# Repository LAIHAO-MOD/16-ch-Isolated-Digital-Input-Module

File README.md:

# 16-ch-Isolated-Digital-Input-Module

16-ch isolated digital input module for DIY cnc system (MACH3 &amp; etc...)

Design for 12V inputs !!! Change input resistors before use in other voltage !!!

Use  KICAD 5.1 as Schematic & Pcb design software .

Production Gerber files will be  include after test run .

layout

3d rendering

pcb

assembled

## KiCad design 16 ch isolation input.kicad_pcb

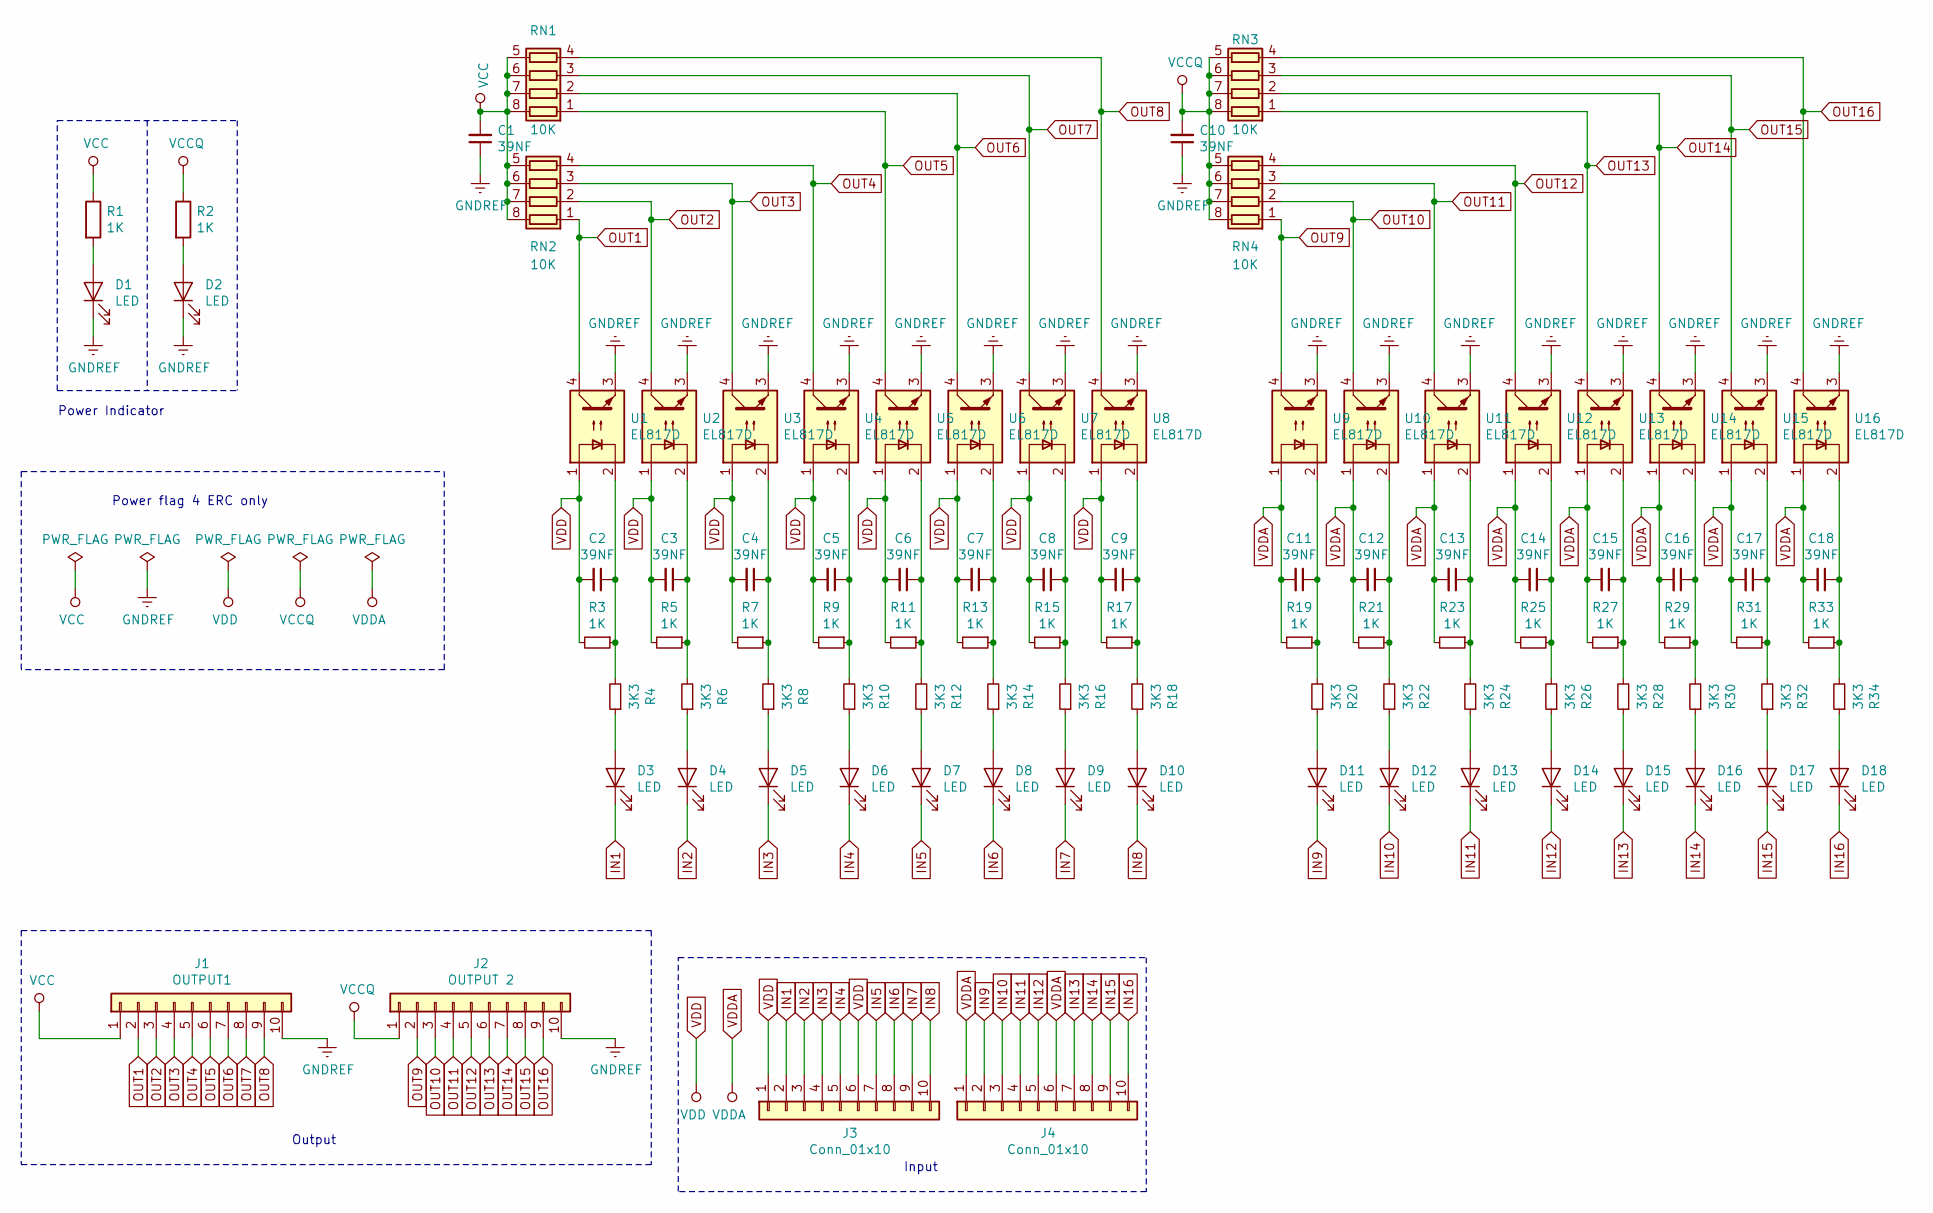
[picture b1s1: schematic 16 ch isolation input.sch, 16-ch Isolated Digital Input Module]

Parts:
C1, C2, C3, C4, C5, C6, C7, C8, C9, C10, C11, C12, C13, C14, C15, C16, C17, C18: 39NF; C_0603_1608Metric
D1, D2, D3, D4, D5, D6, D7, D8, D9, D10, D11, D12, D13, D14, D15, D16, D17, D18: LED; LED_1206_3216Metric
J1: OUTPUT1; mlx254
J2: OUTPUT 2; mlx254
J3, J4: Conn_01x10; ZIP-10-3.5-5
R1, R2, R3, R5, R7, R9, R11, R13, R15, R17, R19, R21, R23, R25, R27, R29, R31, R33: 1K; R_0603_1608Metric
R4, R6, R8, R10, R12, R14, R16, R18, R20, R22, R24, R26, R28, R30, R32, R34: 3K3; R_0603_1608Metric
RN1, RN2, RN3, RN4: 10K; R_Array_Convex_4x0603
U1, U2, U3, U4, U5, U6, U7, U8, U9, U10, U11, U12, U13, U14, U15, U16: EL817D; DIP-4_W7.62mm

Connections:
GNDREF: C1.1, C10.1, D1.1 (K), D2.1 (K), J1.10, J2.10, U1.3, U2.3, U3.3, U4.3, U5.3, U6.3, U7.3, U8.3, U9.3, U10.3, U11.3, U12.3, U13.3, U14.3, U15.3, U16.3; also elsewhere on the board
IN1: D3.1 (K), J3.2; also elsewhere on the board
IN2: D4.1 (K), J3.3; also elsewhere on the board
IN3: D5.1 (K), J3.4; also elsewhere on the board
IN4: D6.1 (K), J3.5; also elsewhere on the board
IN5: D7.1 (K), J3.7; also elsewhere on the board
IN6: D8.1 (K), J3.8; also elsewhere on the board
IN7: D9.1 (K), J3.9; also elsewhere on the board
IN8: D10.1 (K), J3.10; also elsewhere on the board
IN9: D11.1 (K), J4.2; also elsewhere on the board
IN10: D12.1 (K), J4.3; also elsewhere on the board
IN11: D13.1 (K), J4.4; also elsewhere on the board
IN12: D14.1 (K), J4.5; also elsewhere on the board
IN13: D15.1 (K), J4.7; also elsewhere on the board
IN14: D16.1 (K), J4.8; also elsewhere on the board
IN15: D17.1 (K), J4.9; also elsewhere on the board
IN16: D18.1 (K), J4.10; also elsewhere on the board
unnamed: C2.1, R3.1, R4.2, U1.2
unnamed: C3.1, R5.1, R6.2, U2.2
unnamed: C4.1, R7.1, R8.2, U3.2
unnamed: C5.1, R9.1, R10.2, U4.2
unnamed: C6.1, R11.1, R12.2, U5.2
unnamed: C7.1, R13.1, R14.2, U6.2
unnamed: C8.1, R15.1, R16.2, U7.2
unnamed: C9.1, R17.1, R18.2, U8.2
unnamed: C11.1, R19.1, R20.2, U9.2
unnamed: C12.1, R21.1, R22.2, U10.2
unnamed: C13.1, R23.1, R24.2, U11.2
unnamed: C14.1, R25.1, R26.2, U12.2
unnamed: C15.1, R27.1, R28.2, U13.2
unnamed: C16.1, R29.1, R30.2, U14.2
unnamed: C17.1, R31.1, R32.2, U15.2
unnamed: C18.1, R33.1, R34.2, U16.2
unnamed: D1.2 (A), R1.2
unnamed: D2.2 (A), R2.2
unnamed: D3.2 (A), R4.1
unnamed: D4.2 (A), R6.1
unnamed: D5.2 (A), R8.1
unnamed: D6.2 (A), R10.1
unnamed: D7.2 (A), R12.1
unnamed: D8.2 (A), R14.1
unnamed: D9.2 (A), R16.1
unnamed: D10.2 (A), R18.1
unnamed: D11.2 (A), R20.1
unnamed: D12.2 (A), R22.1
unnamed: D13.2 (A), R24.1
unnamed: D14.2 (A), R26.1
unnamed: D15.2 (A), R28.1
unnamed: D16.2 (A), R30.1
unnamed: D17.2 (A), R32.1
unnamed: D18.2 (A), R34.1
OUT1: J1.2, RN2.1 (R1.1), U1.4; also elsewhere on the board
OUT2: J1.3, RN2.2 (R2.1), U2.4; also elsewhere on the board
OUT3: J1.4, RN2.3 (R3.1), U3.4; also elsewhere on the board
OUT4: J1.5, RN2.4 (R4.1), U4.4; also elsewhere on the board
OUT5: J1.6, RN1.1 (R1.1), U5.4; also elsewhere on the board
OUT6: J1.7, RN1.2 (R2.1), U6.4; also elsewhere on the board
OUT7: J1.8, RN1.3 (R3.1), U7.4; also elsewhere on the board
OUT8: J1.9, RN1.4 (R4.1), U8.4; also elsewhere on the board
OUT9: J2.2, RN4.1 (R1.1), U9.4; also elsewhere on the board
OUT10: J2.3, RN4.2 (R2.1), U10.4; also elsewhere on the board
OUT11: J2.4, RN4.3 (R3.1), U11.4; also elsewhere on the board
OUT12: J2.5, RN4.4 (R4.1), U12.4; also elsewhere on the board
OUT13: J2.6, RN3.1 (R1.1), U13.4; also elsewhere on the board
OUT14: J2.7, RN3.2 (R2.1), U14.4; also elsewhere on the board
OUT15: J2.8, RN3.3 (R3.1), U15.4; also elsewhere on the board
OUT16: J2.9, RN3.4 (R4.1), U16.4; also elsewhere on the board
VCC: C1.2, J1.1, R1.1, RN1.5 (R4.2), RN1.6 (R3.2), RN1.7 (R2.2), RN1.8 (R1.2), RN2.5 (R4.2), RN2.6 (R3.2), RN2.7 (R2.2), RN2.8 (R1.2); also elsewhere on the board
VCCQ: C10.2, J2.1, R2.1, RN3.5 (R4.2), RN3.6 (R3.2), RN3.7 (R2.2), RN3.8 (R1.2), RN4.5 (R4.2), RN4.6 (R3.2), RN4.7 (R2.2), RN4.8 (R1.2); also elsewhere on the board
VDD: C2.2, C3.2, C4.2, C5.2, C6.2, C7.2, C8.2, C9.2, J3.1, J3.6, R3.2, R5.2, R7.2, R9.2, R11.2, R13.2, R15.2, R17.2, U1.1, U2.1, U3.1, U4.1, U5.1, U6.1, U7.1, U8.1; also elsewhere on the board
VDDA: C11.2, C12.2, C13.2, C14.2, C15.2, C16.2, C17.2, C18.2, J4.1, J4.6, R19.2, R21.2, R23.2, R25.2, R27.2, R29.2, R31.2, R33.2, U9.1, U10.1, U11.1, U12.1, U13.1, U14.1, U15.1, U16.1; also elsewhere on the board

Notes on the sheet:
Power Indicator
Power flag 4 ERC only
Output
Input

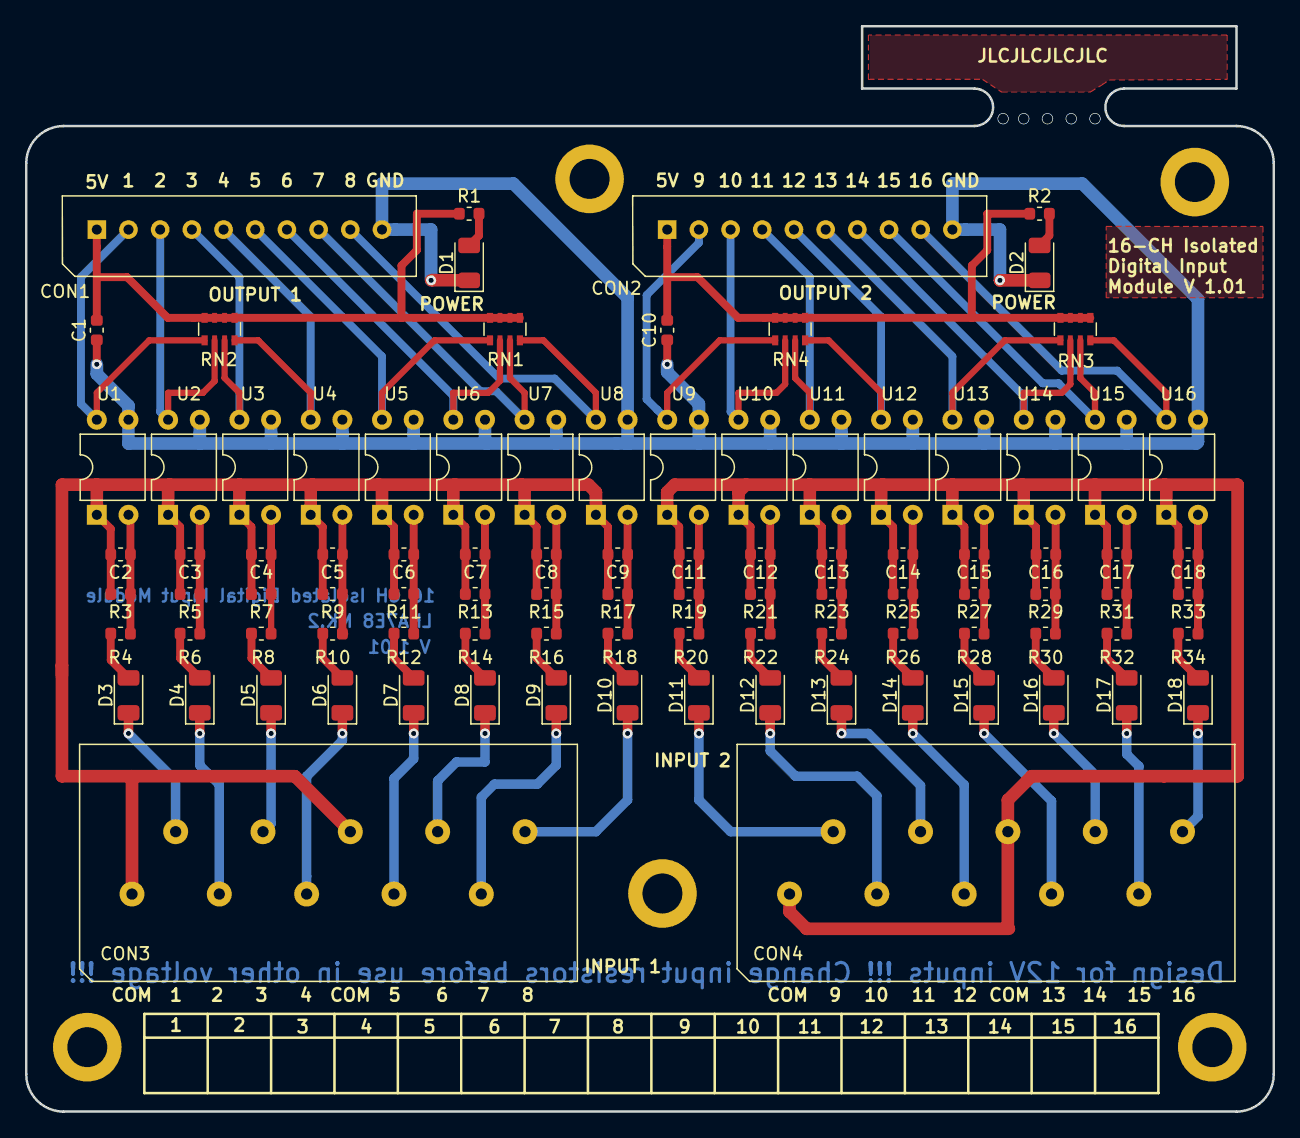
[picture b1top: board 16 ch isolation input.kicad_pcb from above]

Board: 2 copper layers, 100.0 x 87.0 mm, 94 parts (0 on the bottom side), 71 nets.

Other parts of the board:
CON1: OUTPUT1; mlx254
CON2: OUTPUT 2; mlx254
CON3, CON4: Conn_01x10; ZIP-10-3.5-5

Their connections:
GNDREF: CON1.10, CON2.10; also elsewhere on the board
IN1: CON3.2; also elsewhere on the board
IN2: CON3.3; also elsewhere on the board
IN3: CON3.4; also elsewhere on the board
IN4: CON3.5; also elsewhere on the board
IN5: CON3.7; also elsewhere on the board
IN6: CON3.8; also elsewhere on the board
IN7: CON3.9; also elsewhere on the board
IN8: CON3.10; also elsewhere on the board
IN9: CON4.2; also elsewhere on the board
IN10: CON4.3; also elsewhere on the board
IN11: CON4.4; also elsewhere on the board
IN12: CON4.5; also elsewhere on the board
IN13: CON4.7; also elsewhere on the board
IN14: CON4.8; also elsewhere on the board
IN15: CON4.9; also elsewhere on the board
IN16: CON4.10; also elsewhere on the board
OUT1: CON1.2; also elsewhere on the board
OUT2: CON1.3; also elsewhere on the board
OUT3: CON1.4; also elsewhere on the board
OUT4: CON1.5; also elsewhere on the board
OUT5: CON1.6; also elsewhere on the board
OUT6: CON1.7; also elsewhere on the board
OUT7: CON1.8; also elsewhere on the board
OUT8: CON1.9; also elsewhere on the board
OUT9: CON2.2; also elsewhere on the board
OUT10: CON2.3; also elsewhere on the board
OUT11: CON2.4; also elsewhere on the board
OUT12: CON2.5; also elsewhere on the board
OUT13: CON2.6; also elsewhere on the board
OUT14: CON2.7; also elsewhere on the board
OUT15: CON2.8; also elsewhere on the board
OUT16: CON2.9; also elsewhere on the board
VCC: CON1.1; also elsewhere on the board
VCCQ: CON2.1; also elsewhere on the board
VDD: CON3.1, CON3.6; also elsewhere on the board
VDDA: CON4.1, CON4.6; also elsewhere on the board

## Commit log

2019-05-12 add file
    Add project file and reference Datasheet
2019-12-31 Create 1
2019-12-31 Rename 16 ch isolation input to kicad project file/16 ch isolation input
2019-12-31 Rename 16 ch isolation input-cache.lib to kicad project file/16 ch isolation input-cache.lib
2019-12-31 Rename 16 ch isolation input.kicad_pcb to kicad project file/16 ch isolation input.kicad_pcb
2019-12-31 Rename 16 ch isolation input.net to kicad project file/16 ch isolation input.net
2019-12-31 Rename 16 ch isolation input.pro to kicad project file/16 ch isolation input.pro
2019-12-31 Rename 16 ch isolation input.sch to kicad project file/16 ch isolation input.sch
2019-12-31 Rename 16 ch isolation input.xml to kicad project file/16 ch isolation input.xml
2019-12-31 Rename ZIP-10-3.5-5.kicad_mod to kicad project file/ZIP-10-3.5-5.kicad_mod
2019-12-31 Rename mlx254.kicad_mod to kicad project file/mlx254.kicad_mod
2019-12-31 Rename 16ch outline.DXF to 3d/16ch outline.DXF
2019-12-31 Add Production Gerber files
